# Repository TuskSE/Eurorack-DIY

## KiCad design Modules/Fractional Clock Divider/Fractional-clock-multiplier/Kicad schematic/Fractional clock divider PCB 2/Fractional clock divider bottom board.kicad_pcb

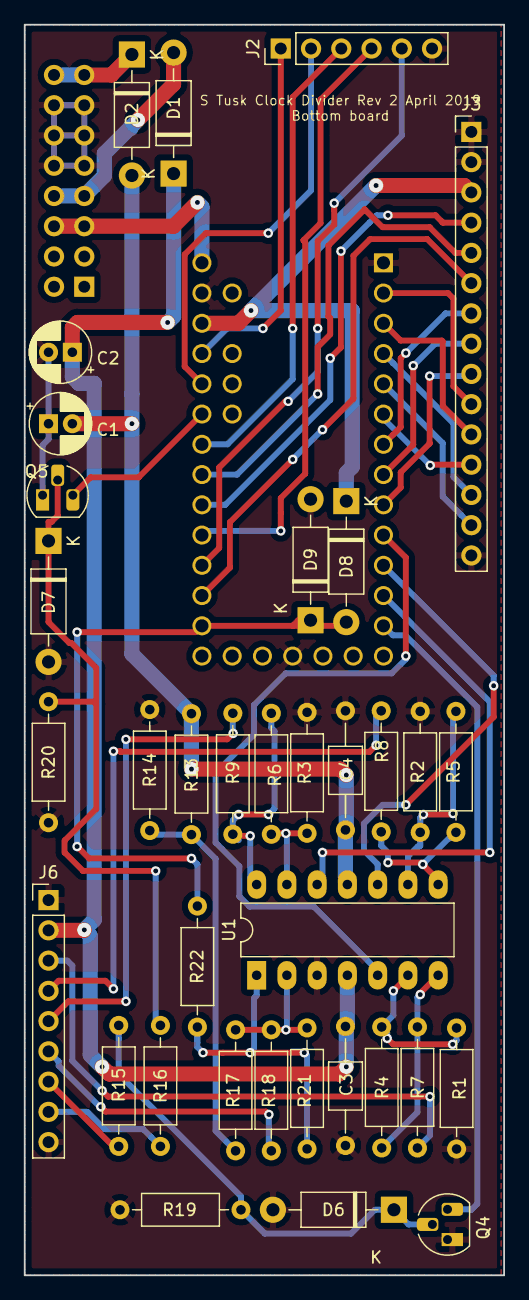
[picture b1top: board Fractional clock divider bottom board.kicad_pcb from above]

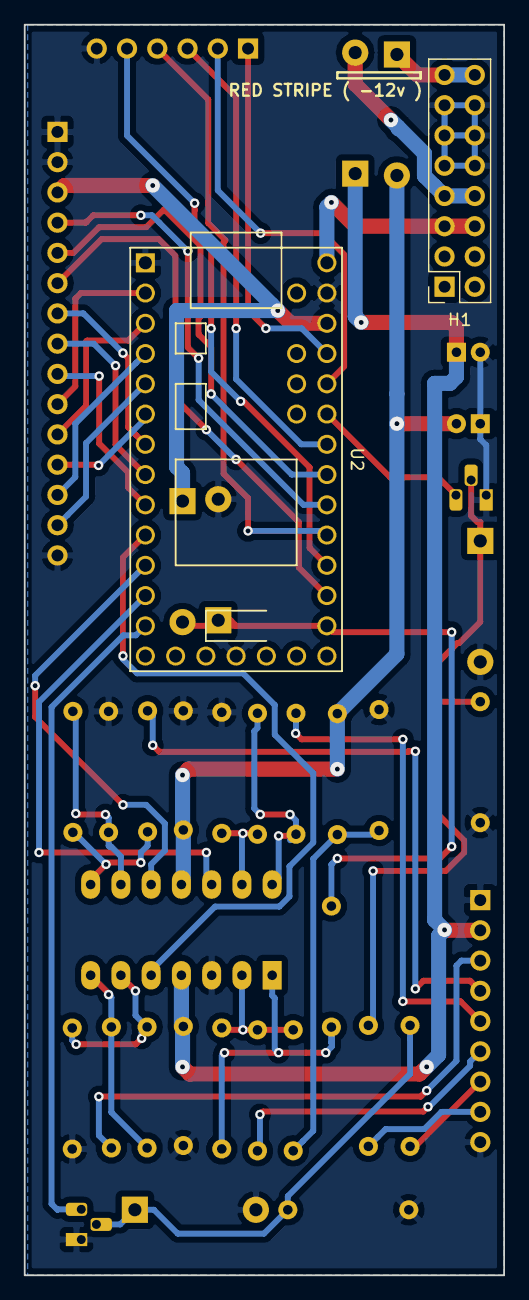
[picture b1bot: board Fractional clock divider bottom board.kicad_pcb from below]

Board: 2 copper layers, 40.2 x 105.0 mm, 37 parts (2 on the bottom side), 46 nets.

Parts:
C1, C2: 10uF; CP_Radial_D5.0mm_P2.00mm
C3, C4: 100nF; C_Axial_L3.8mm_D2.6mm_P10.00mm_Horizontal
D1, D2, D6, D7, D8, D9: 1N4001; D_DO-41_SOD81_P10.16mm_Horizontal
H1: EURO_PWR_2X8; PinSocket_2x08_P2.54mm_Vertical
J2: Conn_01x06_Male; PinHeader_1x06_P2.54mm_Vertical
J3: Conn_01x15_Male; PinHeader_1x15_P2.54mm_Vertical
J6: Conn_01x09_Male; PinHeader_1x09_P2.54mm_Vertical
Q4, Q5: 2N3904; TO-92L_HandSolder
R1, R2, R3, R15, R16, R17, R18: 100k; R_Axial_DIN0207_L6.3mm_D2.5mm_P10.16mm_Horizontal
R4, R5, R6: 47k; R_Axial_DIN0207_L6.3mm_D2.5mm_P10.16mm_Horizontal
R7, R8, R9: 1k; R_Axial_DIN0207_L6.3mm_D2.5mm_P10.16mm_Horizontal
R13: 11k; R_Axial_DIN0207_L6.3mm_D2.5mm_P10.16mm_Horizontal
R14: 91k; R_Axial_DIN0207_L6.3mm_D2.5mm_P10.16mm_Horizontal
R19, R20: 33k; R_Axial_DIN0207_L6.3mm_D2.5mm_P10.16mm_Horizontal
R21: 15k; R_Axial_DIN0207_L6.3mm_D2.5mm_P10.16mm_Horizontal
R22: 10k; R_Axial_DIN0207_L6.3mm_D2.5mm_P10.16mm_Horizontal
U1: TL074; DIP-14_W7.62mm_LongPads
U2: Teensy-LC; TeensyLC_fixed_pads

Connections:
+5V: H1.5, H1.6, U2.33
+12V: C1.1, C3.2, D1.1, J6.2, U1.4
-12V: C2.2, C4.1, D2.2, R13.2, U1.11
/+3_3V: D8.1, J3.3, U2.31
/+12V_in: D1.2, H1.7, H1.8
/-12V_in: D2.1, H1.15, H1.16
/CLin_B: J6.7, R15.2
/CV_in: D8.2, D9.1, R22.1, U2.21
/CV_ind_LED_Divs: J2.2, U2.29
/CV_ind_LED_Length: J2.1, U2.30
/CV_ind_LED_shift: J2.3, U2.27
/CV_ind_LED_shuffle: J2.4, U2.24
/CVin_B: J6.6, R18.2
/Cycle_in: Q5.3, U2.28
/DigiOut_Cycle: U1.5, U2.10
/DigiOut_Thru: U1.12, U2.12
/DigiOut_out: U1.10, U2.11
/EncoderA: J3.7, U2.7
/EncoderB: J3.8, U2.8
/EncoderSw: J3.9, U2.9
/LED_Sh_B: J2.5, U2.23
/OutC_B: J6.3, R7.1
/OutM_B: J6.4, R8.1
/OutT_B: J6.5, R9.1
/Pot_CVamt: J3.6, U2.22
/Pot_Divisions: J3.5, U2.26
/Pot_Length: J3.4, U2.25
/Rin_B: J6.8, R16.2
/SW_CVassgn: J3.12, U2.6
/SW_DivEuc1: J3.10, U2.2
/SW_DivEuc2: J3.11, U2.3
/SW_OutMode1: J3.13, U2.4
/SW_OutMode2: J3.14, U2.5
/Trigger_in: Q4.3, U2.13
/Vref: R13.1, R14.2, R17.2
GND: C1.2, C2.1, C3.1, C4.2, D6.2, D7.2, D9.2, H1.9, H1.10, H1.11, H1.12, H1.13, H1.14, J2.6, J3.1, J3.2, J3.15, J6.1, J6.9, Q4.1, Q5.1, R1.2, R2.2, R3.2, R14.1, R19.1, R20.1, U1.3, U2.1, U2.17, U2.32
unnamed: D6.1, Q4.2, R15.1, R19.2
unnamed: D7.1, Q5.2, R16.1, R20.2
unnamed: R1.1, R4.2, U1.6
unnamed: R2.1, R5.2, U1.9
unnamed: R3.1, R6.2, U1.13
unnamed: R4.1, R7.2, U1.7
unnamed: R5.1, R8.2, U1.8
unnamed: R6.1, R9.2, U1.14
unnamed: R17.1, R18.1, R21.2, U1.2
unnamed: R21.1, R22.2, U1.1

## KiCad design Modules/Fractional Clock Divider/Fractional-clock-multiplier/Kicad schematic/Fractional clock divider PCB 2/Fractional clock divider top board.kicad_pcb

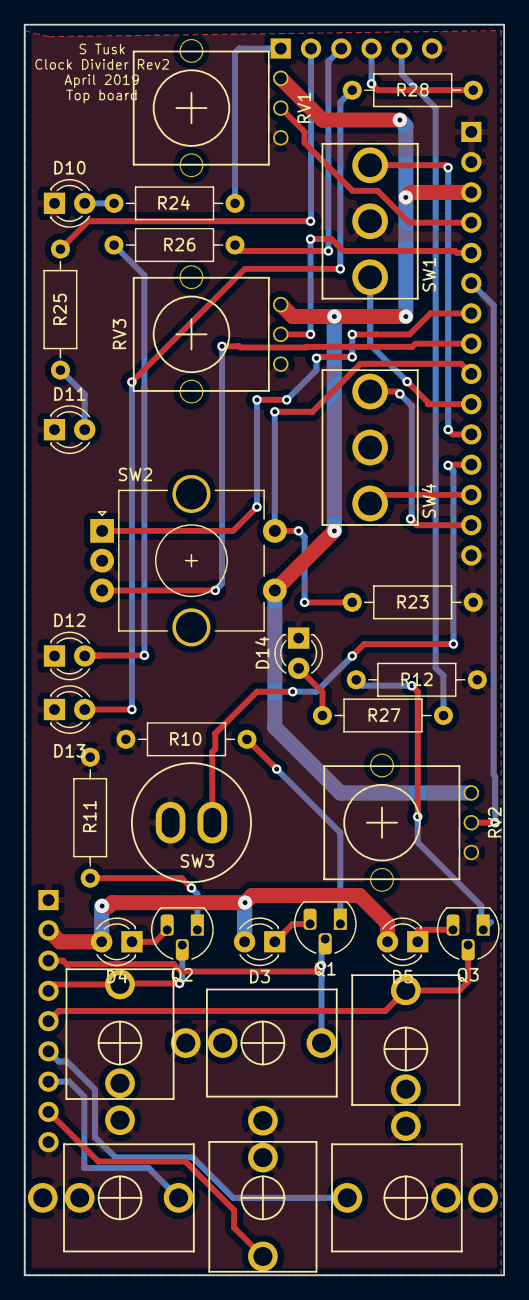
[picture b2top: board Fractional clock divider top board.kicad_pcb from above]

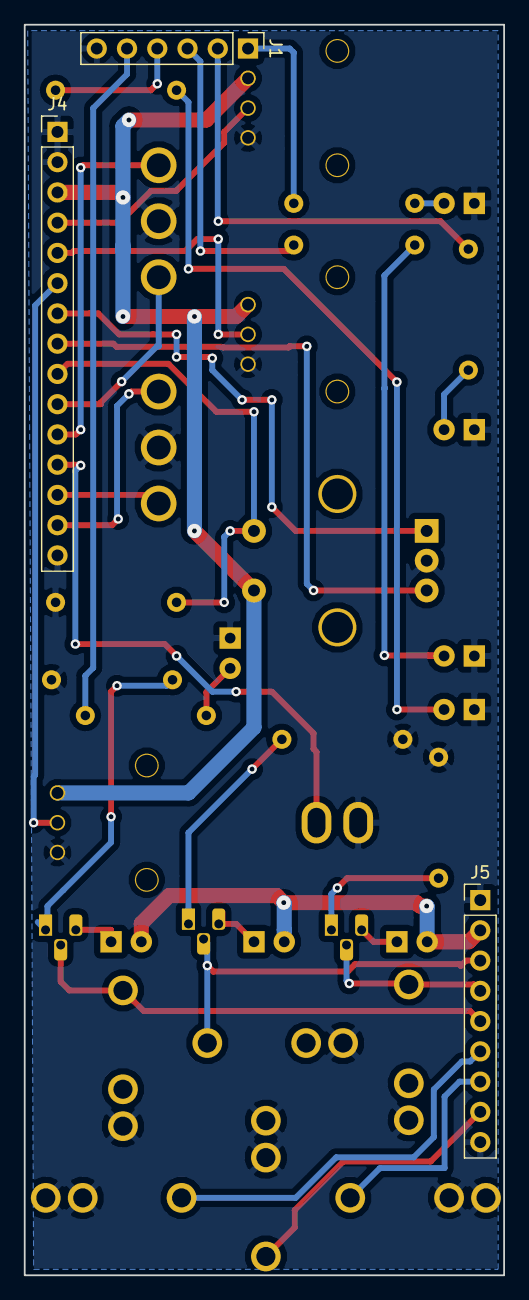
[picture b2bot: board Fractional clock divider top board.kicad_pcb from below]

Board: 2 copper layers, 40.2 x 105.0 mm, 36 parts (3 on the bottom side), 36 nets.

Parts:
CV_in1: PJ301M-12; PJ301M-12-MoreMetal
CycleOutJack1: PJ301M-12; PJ301M-12-MoreMetal
D3, D4, D5, D10, D11, D12, D13, D14: LED; LED_D3.0mm
DigiOutJack1: PJ301M-12; PJ301M-12-MoreMetal
DigiThruJack1: PJ301M-12; PJ301M-12-MoreMetal
J1: Conn_01x06_Female; PinHeader_1x06_P2.54mm_Vertical
J4: Conn_01x15_Female; PinHeader_1x15_P2.54mm_Vertical
J5: Conn_01x09_Female; PinHeader_1x09_P2.54mm_Vertical
Q1, Q2, Q3: 2N3904; TO-92L_HandSolder
R10, R11, R12: 10k; R_Axial_DIN0207_L6.3mm_D2.5mm_P10.16mm_Horizontal
R23: 100k; R_Axial_DIN0207_L6.3mm_D2.5mm_P10.16mm_Horizontal
R24, R25, R26, R28: 1k; R_Axial_DIN0207_L6.3mm_D2.5mm_P10.16mm_Horizontal
R27: 330; R_Axial_DIN0207_L6.3mm_D2.5mm_P10.16mm_Horizontal
RV1, RV2, RV3: 10k; Alpha9mmPot
Reset_In1: PJ301M-12; PJ301M-12-MoreMetal
SW1, SW4: SW_SPDT_MSM; SPDT toggle on-off-on
SW2: Rotary_Encoder_Switch; RotaryEncoder_Alps_EC11E-Switch_Vertical_H20mm_CircularMoun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
SW3: SW_SPST; SPST momentary push PBS105
Trigger/Clock_in1: PJ301M-12; PJ301M-12-MoreMetal

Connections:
+12V: D3.2, D4.2, D5.2, J5.2
/+3_3V: J4.3, RV1.3, RV2.3, RV3.3, SW2.S1
/CLin_F: J5.7, Trigger/Clock_in1.3
/CVin_F: CV_in1.3, J5.6
/EncoderA_F: J4.7, SW2.A
/EncoderB_F: J4.8, SW2.B
/EncoderSw_F: J4.9, R23.1, SW2.S2
/LED_D_F: J1.2, R25.2
/LED_L_F: J1.1, R24.2
/LED_Sh_F: J1.5, R27.2
/Led_ShCV_F: J1.4, R28.2
/Led_Shi_F: J1.3, R26.2
/OutC_F: CycleOutJack1.3, J5.3, Q1.2
/OutM_F: DigiOutJack1.3, J5.4, Q2.2
/OutT_F: DigiThruJack1.3, J5.5, Q3.2
/Pot_CVamt_F: J4.6, RV2.2
/Pot_Divisions_F: J4.5, RV3.2
/Pot_Length_F: J4.4, RV1.2
/Rin_F: J5.8, Reset_In1.3
/SW_CVassgn_F: J4.12, SW3.2
/SW_DivEuc1_F: J4.10, SW1.1
/SW_DivEuc2_F: J4.11, SW1.3
/SW_OutMode1_F: J4.13, SW4.1
/SW_OutMode2_F: J4.14, SW4.3
GND: CV_in1.1, CV_in1.2, CycleOutJack1.1, D10.1, D11.1, D12.1, D13.1, D14.1, DigiOutJack1.1, DigiThruJack1.1, J1.6, J4.1, J4.2, J4.15, J5.1, J5.9, R10.1, R11.1, R12.1, R23.2, RV1.1, RV2.1, RV3.1, Reset_In1.1, Reset_In1.2, SW1.2, SW2.C, SW3.1, SW4.2, Trigger/Clock_in1.1, Trigger/Clock_in1.2
unnamed: D3.1, Q1.3
unnamed: D4.1, Q2.3
unnamed: D5.1, Q3.3
unnamed: D10.2, R24.1
unnamed: D11.2, R25.1
unnamed: D12.2, R26.1
unnamed: D13.2, R28.1
unnamed: D14.2, R27.1
unnamed: Q1.1, R10.2
unnamed: Q2.1, R11.2
unnamed: Q3.1, R12.2

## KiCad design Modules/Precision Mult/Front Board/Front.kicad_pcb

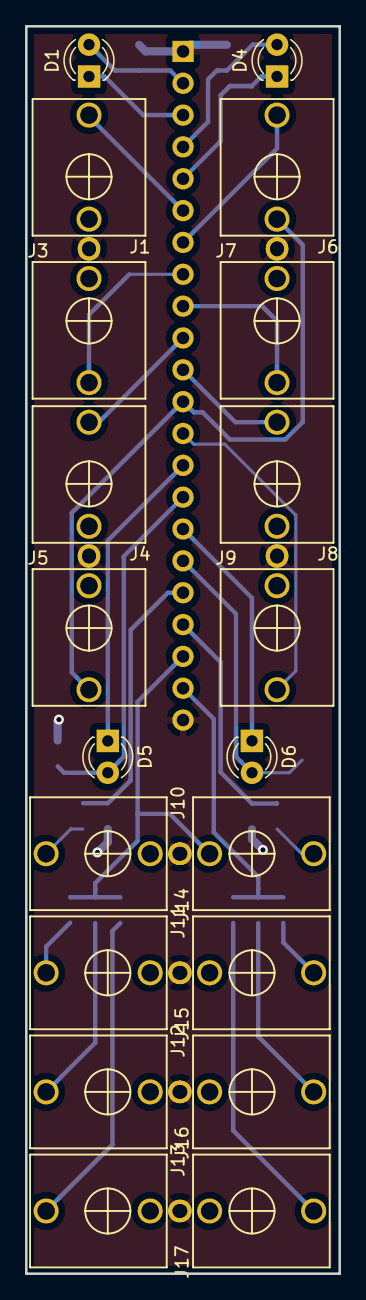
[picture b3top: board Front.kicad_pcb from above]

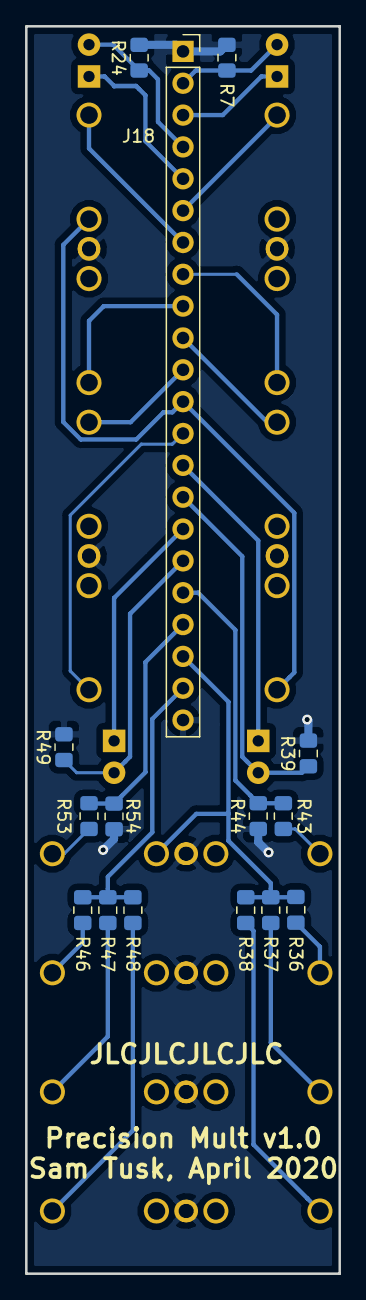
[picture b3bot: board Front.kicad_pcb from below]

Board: 2 copper layers, 25.0 x 99.5 mm, 35 parts (15 on the bottom side), 29 nets.

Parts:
D1, D4, D5, D6: Tayda A-1076; LED_D3.0mm
J1, J3, J4, J5, J6, J7, J8, J9, J10, J11, J12, J13, J14, J15, J16, J17: PJ301M-12; PJ301M-12_Compact
J18: Conn_01x22_Female; PinSocket_1x22_P2.54mm_Vertical
R7, R24, R39, R49: 660R; R_0805_2012Metric_Pad1.15x1.40mm_HandSolder
R36, R37, R38, R46, R47, R48: 1k; R_0805_2012Metric_Pad1.15x1.40mm_HandSolder
R43, R44, R53, R54: 100K; R_0805_2012Metric_Pad1.15x1.40mm_HandSolder

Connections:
/B3out1: J11.3, R36.1
/B3out2: J12.3, R37.1
/B3out3: J13.3, R38.1
/B4out1: J15.3, R46.1
/B4out2: J16.3, R47.1
/B4out3: J17.3, R48.1
B1L1F: D1.1, J18.3
B1L2F: D1.2, J18.2, R7.1
B1O1F: J3.3, J18.8
B1O2F: J4.3, J18.10
B1O3F: J5.3, J6.2, J18.12
B1inF: J1.3, J18.6
B2L1F: D4.1, J18.5
B2L2F: D4.2, J18.4, R24.1
B2O1F: J7.3, J18.9
B2O2F: J8.3, J18.11
B2O3F: J9.3, J18.13
B2inF: J6.3, J18.7
B3L1F: D5.1, J18.14
B3L2F: D5.2, J18.15, R39.1
B3inF: J18.18, R43.1, R44.2
B3outF: J14.2, J18.20, R36.2, R37.2, R38.2
B4L1F: D6.1, J18.16
B4L2F: D6.2, J18.17, R49.1
B4inF: J18.19, R53.1, R54.2
B4outF: J18.21, R46.2, R47.2, R48.2
GND: J1.1, J3.1, J4.1, J5.1, J6.1, J7.1, J8.1, J9.1, J10.1, J11.1, J12.1, J13.1, J14.1, J15.1, J16.1, J17.1, J18.1, J18.22, R7.2, R24.2, R39.2, R44.1, R49.2, R54.1
unnamed: J10.3, R43.2
unnamed: J14.3, R53.2

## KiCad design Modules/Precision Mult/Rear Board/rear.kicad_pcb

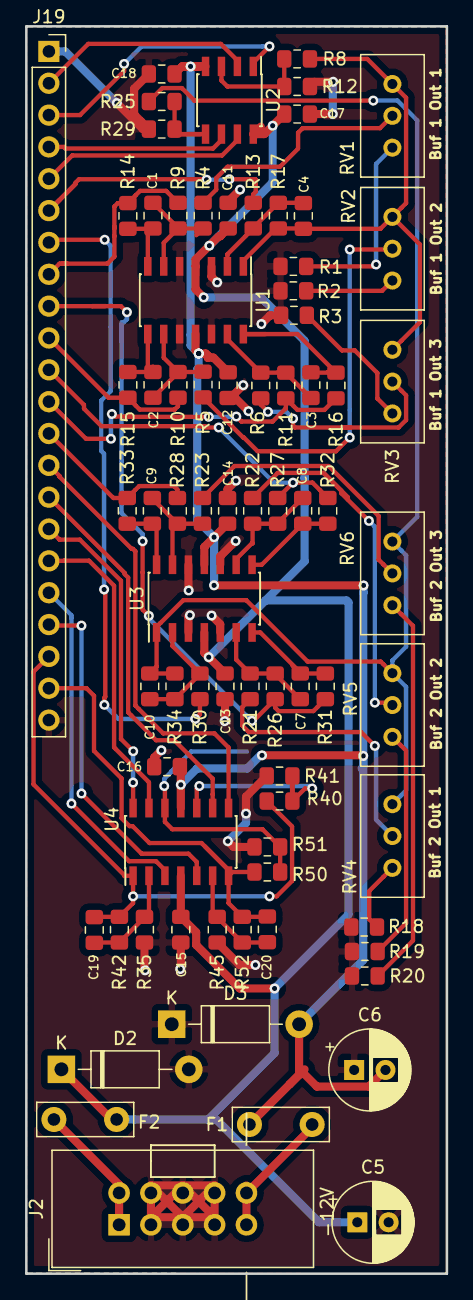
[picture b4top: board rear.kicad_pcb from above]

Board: 2 copper layers, 33.5 x 99.5 mm, 76 parts (0 on the bottom side), 59 nets.

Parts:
C1, C2, C3, C4, C7, C8, C9, C10, C19, C20: 10pF; C_0805_2012Metric_Pad1.15x1.40mm_HandSolder_smallText
C5, C6: 100uF; CP_Radial_D6.3mm_P2.50mm
C11, C12, C13, C14, C15, C16, C17, C18: 100nF; C_0805_2012Metric_Pad1.15x1.40mm_HandSolder_smallText
D2, D3: 1N4001; D_DO-41_SOD81_P10.16mm_Horizontal
F1, F2: Polyfuse 250mA (A-1391); C_Disc_D7.5mm_W2.5mm_P5.00mm
J2: EURO_PWR_2x5; Eurorack_power_header
J19: Conn_01x22_Male; PinSocket_1x22_P2.54mm_Vertical
R1, R2, R3, R18, R19, R20: 10k; R_0805_2012Metric_Pad1.15x1.40mm_HandSolder
R4, R5, R6, R21, R22, R23: 47k; R_0805_2012Metric_Pad1.15x1.40mm_HandSolder
R8, R12, R25, R29, R40, R41, R50, R51: 1M; R_0805_2012Metric_Pad1.15x1.40mm_HandSolder
R9, R10, R11, R26, R27, R28: 51k; R_0805_2012Metric_Pad1.15x1.40mm_HandSolder
R13, R17, R30, R34, R35, R42, R45, R52: 100K; R_0805_2012Metric_Pad1.15x1.40mm_HandSolder
R14, R15, R16, R31, R32, R33: 220R; R_0805_2012Metric_Pad1.15x1.40mm_HandSolder
RV1, RV2, RV3, RV4, RV5, RV6: 2k; Potentiometer_Bourns_3296W_Vertical
U1, U3, U4: TL074; SOIC-14_3.9x8.7mm_P1.27mm
U2: TL072; SOIC-8_3.9x4.9mm_P1.27mm

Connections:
+12V: C5.1, C11.2, C13.2, C15.2, C17.2, D2.1, F2.1, U1.4, U2.8, U3.4, U4.4
-12V: C6.2, C12.1, C14.1, C16.1, C18.1, D3.2, F1.2, U1.11, U2.4, U3.11, U4.11
/+12Vin: F2.2, J2.1, J2.2
/-12Vin: F1.1, J2.9, J2.10
B1L1: J19.3, U2.1
B1L2: J19.2, U2.2
B1O1: J19.8, R9.2, R14.1
B1O2: J19.10, R10.2, R15.1
B1O3: J19.12, R11.2, R16.1
B1S1: C4.1, R8.2, R17.1, RV1.1, RV2.1, RV3.1, U1.1
B1in: J19.6, R13.2
B2L1: J19.5, U2.7
B2L2: J19.4, U2.6
B2O1: J19.9, R26.2, R31.1
B2O2: J19.11, R27.2, R32.1
B2O3: J19.13, R28.2, R33.1
B2S1: C10.1, R25.2, R34.1, RV4.1, RV5.1, RV6.1, U3.1
B2in: J19.7, R30.2
B3L1: J19.14, U4.8
B3L2: J19.15, U4.9
B3in: J19.18, U4.3
B3out: C19.1, J19.20, R40.2, R42.1, U4.1
B4L1: J19.16, U4.14
B4L2: J19.17, U4.13
B4in: J19.19, U4.5
B4out: C20.1, J19.21, R50.2, R52.1, U4.7
GND: C5.2, C6.1, C11.1, C12.2, C13.1, C14.2, C15.1, C16.2, C17.1, C18.2, D2.2, D3.1, J2.3, J2.4, J2.5, J2.6, J2.7, J2.8, J19.1, J19.22, R1.1, R2.1, R3.1, R12.1, R18.1, R19.1, R20.1, R29.1, R35.2, R41.1, R45.2, R51.1, U1.3, U1.5, U1.10, U1.12, U3.3, U3.5, U3.10, U3.12
unnamed: C1.1, R4.2, R9.1, U1.6
unnamed: C1.2, R14.2, U1.7
unnamed: C2.1, R5.2, R10.1, U1.9
unnamed: C2.2, R15.2, U1.8
unnamed: C3.1, R6.2, R11.1, U1.13
unnamed: C3.2, R16.2, U1.14
unnamed: C4.2, R13.1, R17.2, U1.2
unnamed: C7.1, R21.2, R26.1, U3.6
unnamed: C7.2, R31.2, U3.7
unnamed: C8.1, R22.2, R27.1, U3.9
unnamed: C8.2, R32.2, U3.8
unnamed: C9.1, R23.2, R28.1, U3.13
unnamed: C9.2, R33.2, U3.14
unnamed: C10.2, R30.1, R34.2, U3.2
unnamed: C19.2, R35.1, R42.2, U4.2
unnamed: C20.2, R45.1, R52.2, U4.6
unnamed: R1.2, RV1.3
unnamed: R2.2, RV2.3
unnamed: R3.2, RV3.3
unnamed: R4.1, RV1.2
unnamed: R5.1, RV2.2
unnamed: R6.1, RV3.2
unnamed: R8.1, R12.2, U2.3
unnamed: R18.2, RV4.3
unnamed: R19.2, RV5.3
unnamed: R20.2, RV6.3
unnamed: R21.1, RV4.2
unnamed: R22.1, RV5.2
unnamed: R23.1, RV6.2
unnamed: R25.1, R29.2, U2.5
unnamed: R40.1, R41.2, U4.10
unnamed: R50.1, R51.2, U4.12

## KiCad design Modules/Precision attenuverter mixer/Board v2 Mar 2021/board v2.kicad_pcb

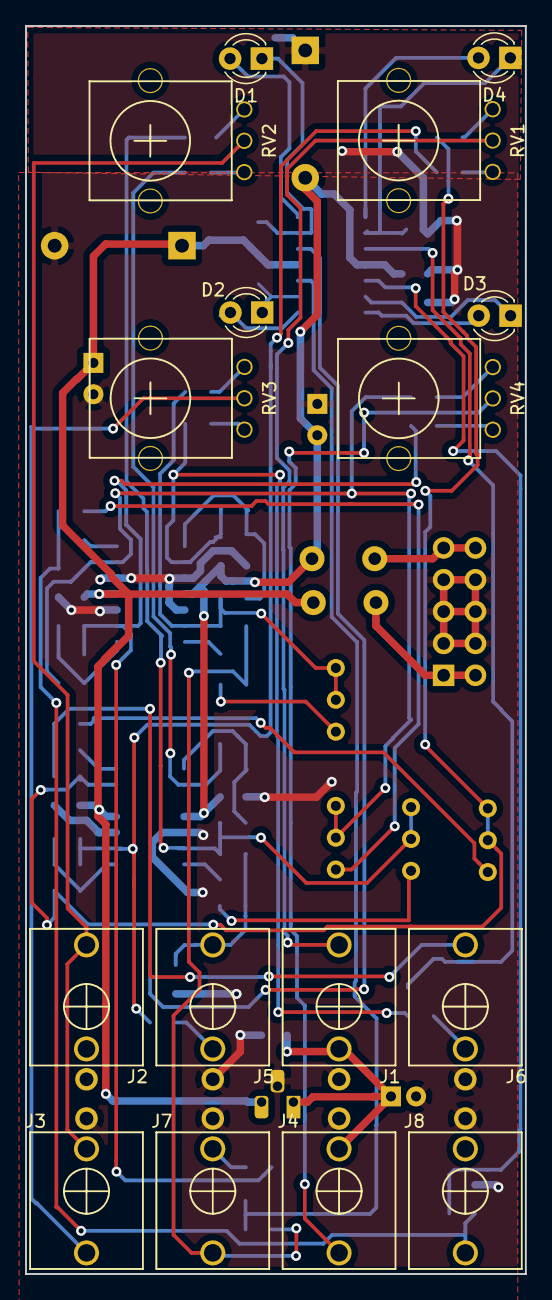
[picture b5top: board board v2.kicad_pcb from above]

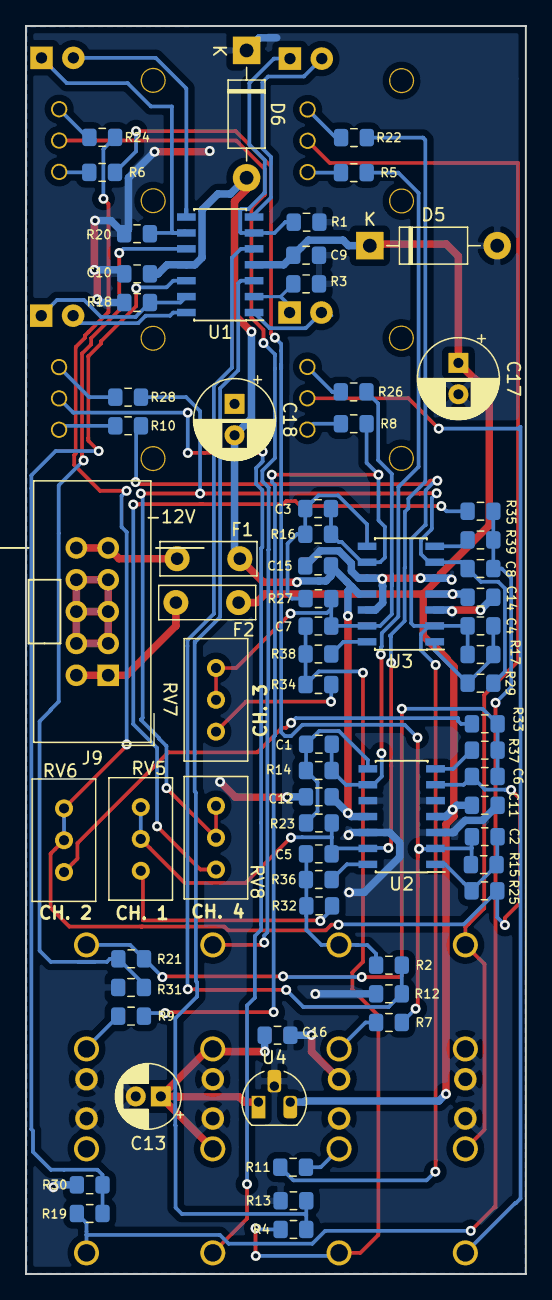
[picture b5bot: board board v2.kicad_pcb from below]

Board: 2 copper layers, 39.9 x 99.6 mm, 86 parts (70 on the bottom side), 57 nets.

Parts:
C1, C2, C3, C4, C5, C6, C7, C8: 10pF; C_0805_2012Metric_Pad1.15x1.40mm_HandSolder_smallText
C9, C10, C11, C12, C14, C15, C16: 100nF; C_0805_2012Metric_Pad1.15x1.40mm_HandSolder_smallText
C13: 10uF; CP_Radial_D5.0mm_P2.00mm
C17, C18: 100uF; CP_Radial_D6.3mm_P2.50mm
D1, D2, D3, D4: Tayda A-1076; LED_D3.0mm
D5, D6: 1N4001; D_DO-41_SOD81_P10.16mm_Horizontal
F1, F2: Polyfuse 250mA (A-1391); C_Disc_D7.5mm_W2.5mm_P5.00mm
J1, J2, J3, J4, J5, J6, J7, J8: PJ301M-12; PJ301M-12_Compact
J9: EURO_PWR_2x5; Eurorack_power_header
R1, R3, R18, R20: 660R; R_0805_2012Metric_Pad1.15x1.40mm_HandSolder_smallText
R2, R4, R12, R13, R19, R21, R30, R31: 1M; R_0805_2012Metric_Pad1.15x1.40mm_HandSolder_smallText
R5, R6, R8, R10, R14, R15, R16, R17, R22, R23, R24, R25, R26, R27, R28, R29: 10k; R_0805_2012Metric_Pad1.15x1.40mm_HandSolder_smallText
R7, R9, R11: 20k; R_0805_2012Metric_Pad1.15x1.40mm_HandSolder_smallText
R32: 9.1k; R_0805_2012Metric_Pad1.15x1.40mm_HandSolder_smallText
R33, R34, R35: 18k; R_0805_2012Metric_Pad1.15x1.40mm_HandSolder_smallText
R36, R37, R38, R39: 220R; R_0805_2012Metric_Pad1.15x1.40mm_HandSolder_smallText
RV1, RV2, RV3, RV4: 100k; Alpha9mmPot
RV5: 2k; Potentiometer_Bourns_3296W_Vertical
RV6, RV7, RV8: 5k; Potentiometer_Bourns_3296W_Vertical
U1, U2, U3: TL074; SOIC-14_3.9x8.7mm_P1.27mm
U4: L78L05_TO92; TO-92_HandSolder

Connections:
+5V: C13.1, C16.2, J1.2, J4.2, U4.1
+12V: C9.2, C11.2, C14.2, C17.1, D5.1, F2.1, U1.4, U2.4, U3.4, U4.3
-12V: C10.1, C12.1, C15.1, C18.2, D6.2, F1.2, U1.11, U2.11, U3.11
/+12Vin: F2.2, J9.1, J9.2
/-12Vin: F1.1, J9.9, J9.10
/Bin: J1.3, RV1.2
/Cin: J3.3, RV3.2
/Din: J4.3, RV4.2
Ain: J2.3, J3.2, RV2.2
Aout: C5.1, J5.3, R2.2, R32.1, R36.1
AoutSw: J5.2, R7.2
Bout: C6.1, J6.3, R21.2, R33.1, R37.1
BoutSw: J6.2, R9.2
Cout: C7.1, J7.3, R4.2, R34.1, R38.1
CoutSw: J7.2, R11.2
Dout: C8.1, J8.3, R19.2, R35.1, R39.1
GND: C9.1, C10.2, C11.1, C12.2, C13.2, C14.1, C15.2, C16.1, C17.2, C18.1, D5.2, D6.1, J1.1, J2.1, J2.2, J3.1, J4.1, J5.1, J6.1, J7.1, J8.1, J9.3, J9.4, J9.5, J9.6, J9.7, J9.8, R1.2, R3.2, R12.1, R13.1, R18.2, R20.2, R30.1, R31.1, U2.3, U2.5, U2.10, U2.12, U3.3, U3.5, U3.10, U3.12, U4.2
unnamed: C1.1, R14.1, R23.2, U2.8
unnamed: C1.2, R5.1, R14.2, U2.9
unnamed: C2.1, R15.1, R25.2, U2.1
unnamed: C2.2, R6.1, R7.1, R15.2, U2.2
unnamed: C3.1, R16.1, R27.2, U3.8
unnamed: C3.2, R8.1, R9.1, R16.2, U3.9
unnamed: C4.1, R17.1, R29.2, U3.1
unnamed: C4.2, R10.1, R11.1, R17.2, U3.2
unnamed: C5.2, R22.1, R23.1, RV5.2, RV5.3, U2.13
unnamed: C6.2, R24.1, R25.1, RV6.2, RV6.3, U2.6
unnamed: C7.2, R26.1, R27.1, RV7.2, RV7.3, U3.13
unnamed: C8.2, R28.1, R29.1, RV8.2, RV8.3, U3.6
unnamed: D1.1, R1.1, U1.6
unnamed: D2.1, R3.1, U1.2
unnamed: D3.1, R18.1, U1.13
unnamed: D4.1, R20.1, U1.9
unnamed: R5.2, RV2.1
unnamed: R6.2, RV1.1
unnamed: R8.2, RV3.1
unnamed: R10.2, RV4.1
unnamed: R2.1, R12.2, U1.5
unnamed: R4.1, R13.2, U1.3
unnamed: R19.1, R30.2, U1.12
unnamed: R21.1, R31.2, U1.10
unnamed: R22.2, RV2.3
unnamed: R24.2, RV1.3
unnamed: R26.2, RV3.3
unnamed: R28.2, RV4.3
unnamed: R32.2, RV5.1
unnamed: R33.2, RV6.1
unnamed: R34.2, RV7.1
unnamed: R35.2, RV8.1
unnamed: R36.2, U2.14
unnamed: R37.2, U2.7
unnamed: R38.2, U3.14
unnamed: R39.2, U3.7
ledA: D1.2, U1.7
ledB: D4.2, U1.8
ledC: D2.2, U1.1
ledD: D3.2, U1.14
